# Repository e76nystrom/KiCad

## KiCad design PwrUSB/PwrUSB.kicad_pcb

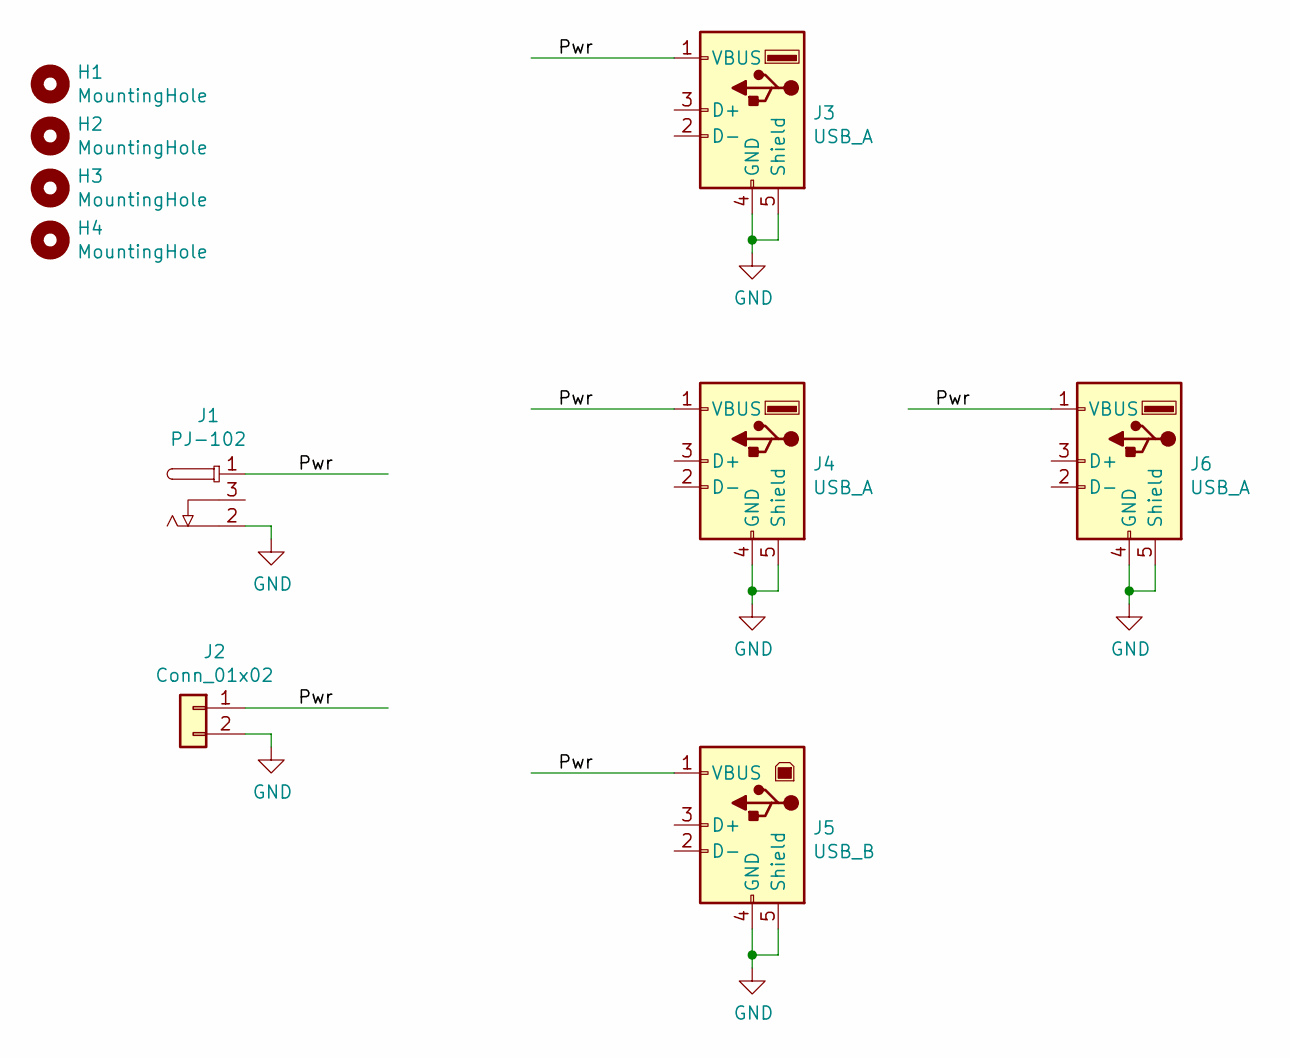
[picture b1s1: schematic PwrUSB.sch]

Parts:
H1, H2, H3, H4: MountingHole; MountingHole _1-8_1-4
J1: PJ-102
J2: Conn_01x02; 2 Pin 3.81mm
J3, J4: USB_A; USB-A
J5: USB_B; USB-B
J6: USB_A; USB-A-Vert

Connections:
/Pwr: J1.1, J2.1, J3.1 (VBUS), J4.1 (VBUS), J5.1 (VBUS), J6.1 (VBUS)
GND: J1.2, J2.2, J3.4 (GND), J3.5 (Shield), J4.4 (GND), J4.5 (Shield), J5.4 (GND), J5.5 (Shield), J6.4 (GND), J6.5 (Shield)

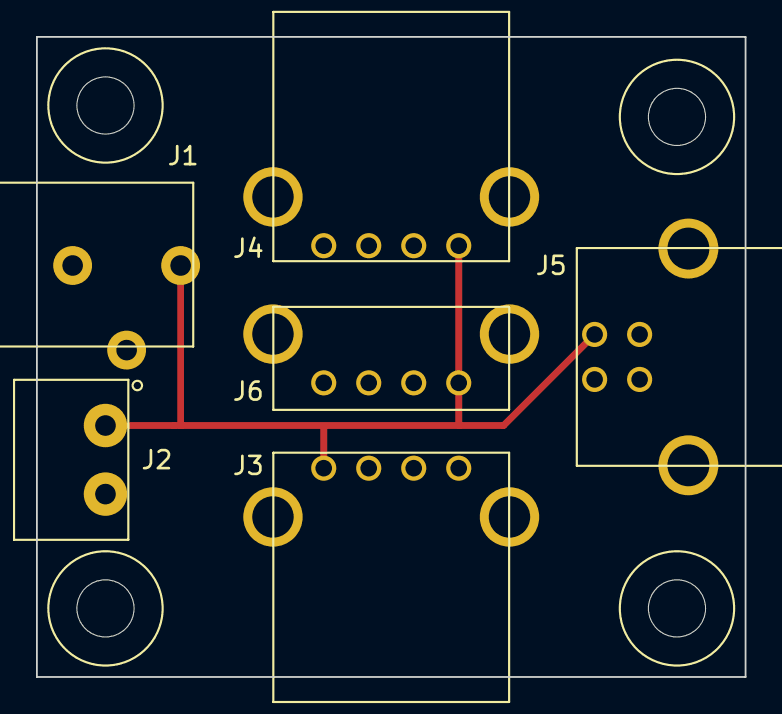
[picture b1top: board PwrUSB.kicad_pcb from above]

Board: 2 copper layers, 39.4 x 35.6 mm, 10 parts (0 on the bottom side), 2 nets.

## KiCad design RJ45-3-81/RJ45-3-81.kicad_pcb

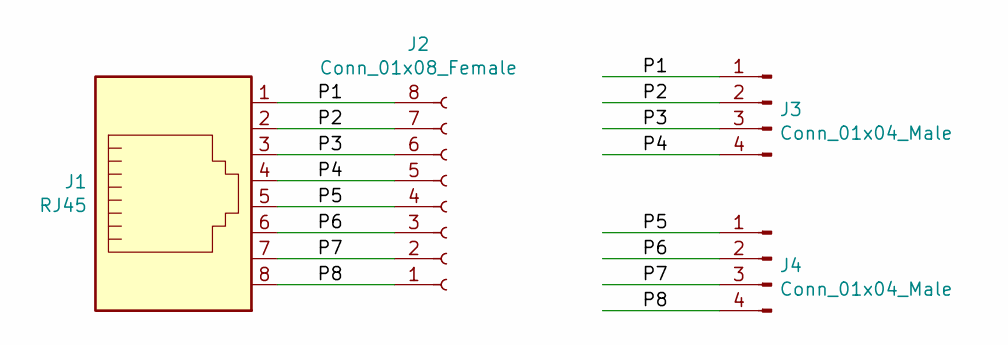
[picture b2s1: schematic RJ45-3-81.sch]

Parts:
J1: RJ45; RJ45_Amphenol_54602-x08_Horizontal
J2: Conn_01x08_Female; PhoenixContact_MC_1,5_8-G-3.81_1x08_P3.81mm_Horizontal
J3, J4: Conn_01x04_Male; PinHeader_1x04_P2.54mm_Vertical

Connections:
/P1: J1.1, J2.8, J3.1
/P2: J1.2, J2.7, J3.2
/P3: J1.3, J2.6, J3.3
/P4: J1.4, J2.5, J3.4
/P5: J1.5, J2.4, J4.1
/P6: J1.6, J2.3, J4.2
/P7: J1.7, J2.2, J4.3
/P8: J1.8, J2.1, J4.4

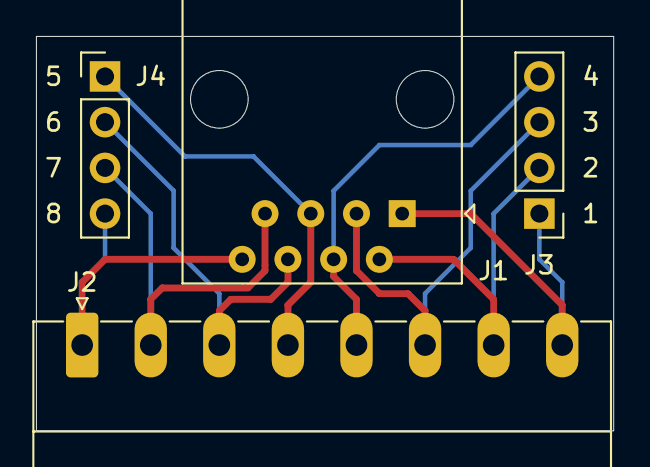
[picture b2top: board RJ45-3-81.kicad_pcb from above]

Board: 2 copper layers, 32.1 x 21.9 mm, 4 parts (0 on the bottom side), 8 nets.

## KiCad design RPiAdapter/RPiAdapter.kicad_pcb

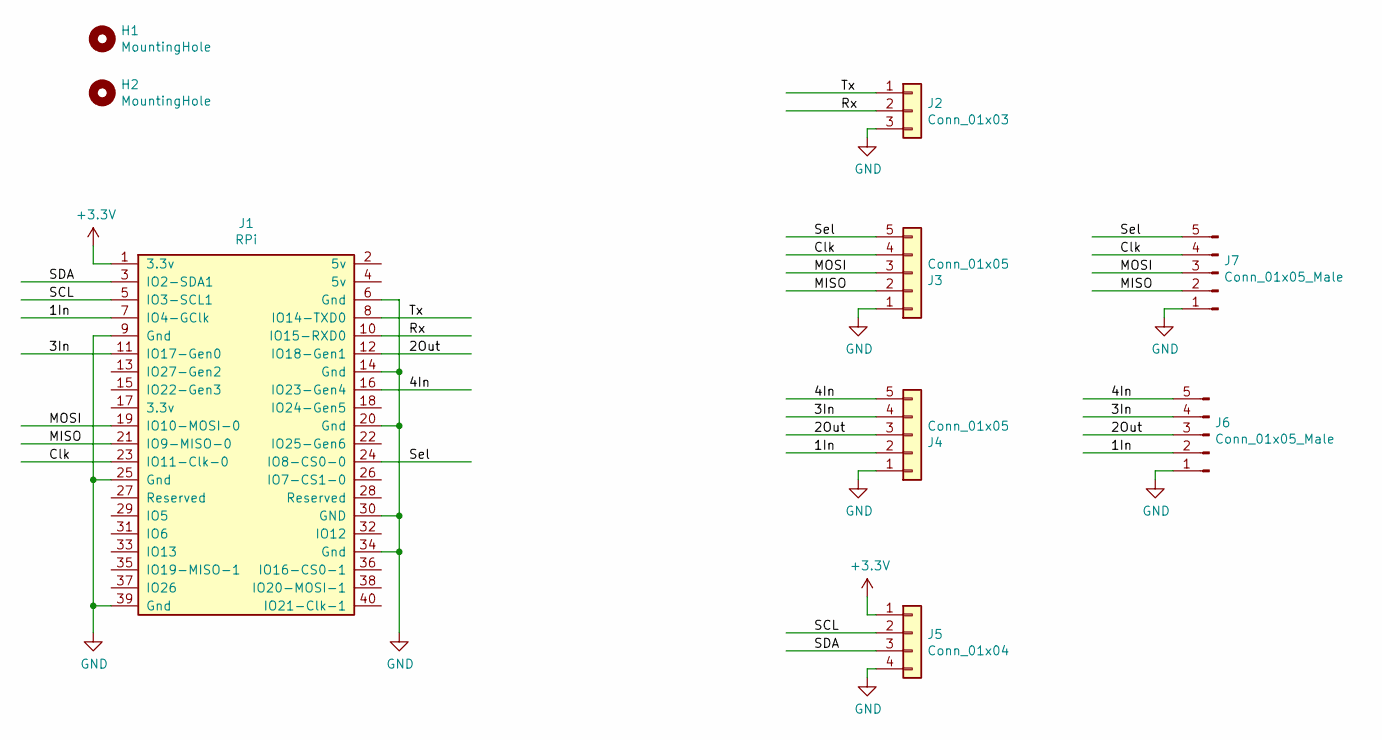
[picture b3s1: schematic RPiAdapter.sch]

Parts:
H1, H2: MountingHole; MountingHole _1-8_1-4
J1: RPi; PinHeader_2x20_P2.54mm_Vertical
J2: Conn_01x03; JST_EH_S3B-EH_1x03_P2.50mm_Horizontal
J3, J4: Conn_01x05; Molex_KK-254_AE-6410-05A_1x05_P2.54mm_Vertical
J5: Conn_01x04; JST_EH_S4B-EH_1x04_P2.50mm_Horizontal
J6, J7: Conn_01x05_Male; PinHeader_1x05_P2.54mm_Vertical

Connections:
+3V3: J1.1 (3.3v), J5.1
/1In: J1.7 (IO4-GClk), J4.2, J6.2
/2Out: J1.12 (IO18-Gen1), J4.3, J6.3
/3In: J1.11 (IO17-Gen0), J4.4, J6.4
/4In: J1.16 (IO23-Gen4), J4.5, J6.5
/Clk: J1.23 (IO11-Clk-0), J3.4, J7.4
/MISO: J1.21 (IO9-MISO-0), J3.2, J7.2
/MOSI: J1.19 (IO10-MOSI-0), J3.3, J7.3
/Rx: J1.10 (IO15-RXD0), J2.2
/SCL: J1.5 (IO3-SCL1), J5.2
/SDA: J1.3 (IO2-SDA1), J5.3
/Sel: J1.24 (IO8-CS0-0), J3.5, J7.5
/Tx: J1.8 (IO14-TXD0), J2.1
GND: J1.6 (Gnd), J1.9 (Gnd), J1.14 (Gnd), J1.20 (Gnd), J1.25 (Gnd), J1.30 (GND), J1.34 (Gnd), J1.39 (Gnd), J2.3, J3.1, J4.1, J5.4, J6.1, J7.1

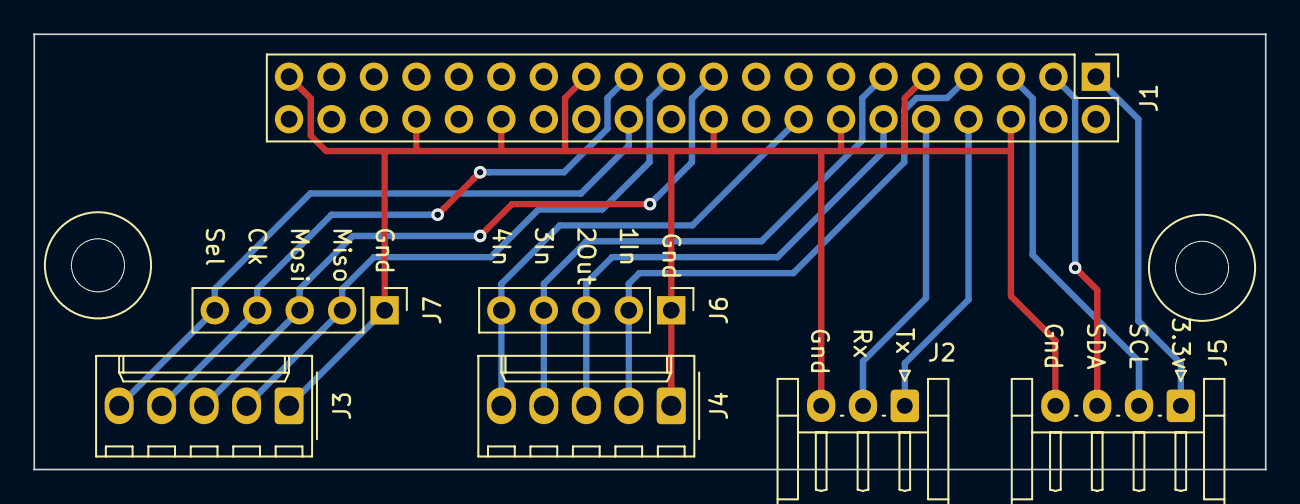
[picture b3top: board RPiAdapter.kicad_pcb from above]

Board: 2 copper layers, 73.7 x 26.0 mm, 9 parts (0 on the bottom side), 14 nets.

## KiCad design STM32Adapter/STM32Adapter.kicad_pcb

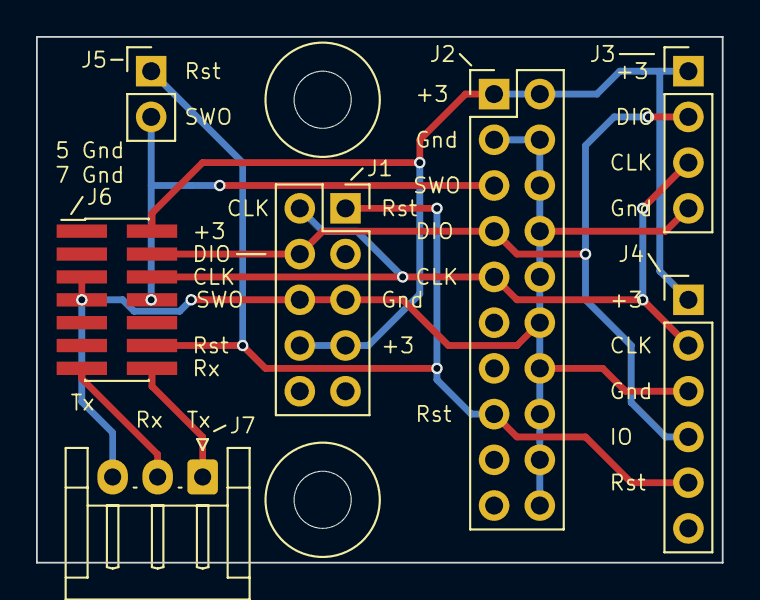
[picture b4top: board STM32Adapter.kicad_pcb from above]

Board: 2 copper layers, 38.1 x 29.2 mm, 9 parts (0 on the bottom side), 8 nets.

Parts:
H1, H2: MountingHole; MountingHole _1-8_1-4
J1: Conn_02x05_Odd_Even; PinSocket_2x05_P2.54mm_Vertical
J2: Conn_02x10_Odd_Even; PinHeader_2x10_P2.54mm_Vertical
J3: Conn_01x04_Male; PinHeader_1x04_P2.54mm_Vertical
J4: Conn_01x06_Male; PinHeader_1x06_P2.54mm_Vertical
J5: Conn_01x02_Male; PinHeader_1x02_P2.54mm_Vertical
J6: Conn_02x07_Odd_Even; PinHeader_2x07_P1.27mm_Vertical_SMD_Samtec
J7: Conn_01x03; JST_EH_S3B-EH_1x03_P2.50mm_Horizontal

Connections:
+3V3: J1.7, J1.8, J2.1, J2.2, J3.1, J4.1, J6.2
/Reset: J1.1, J2.15, J4.5, J5.1, J6.12
/SWCLK: J1.2, J2.9, J3.3, J4.2, J6.6
/SWDIO: J1.4, J2.7, J3.2, J4.4, J6.4
/SWO: J2.5, J5.2, J6.8
/VCP_RX<-TX: J6.14, J7.1
/VCP_TX->RX: J6.13, J7.2
GND: J1.5, J1.6, J2.3, J2.4, J2.6, J2.8, J2.10, J2.12, J2.14, J2.16, J2.18, J2.20, J3.4, J4.3, J6.5, J6.7, J7.3

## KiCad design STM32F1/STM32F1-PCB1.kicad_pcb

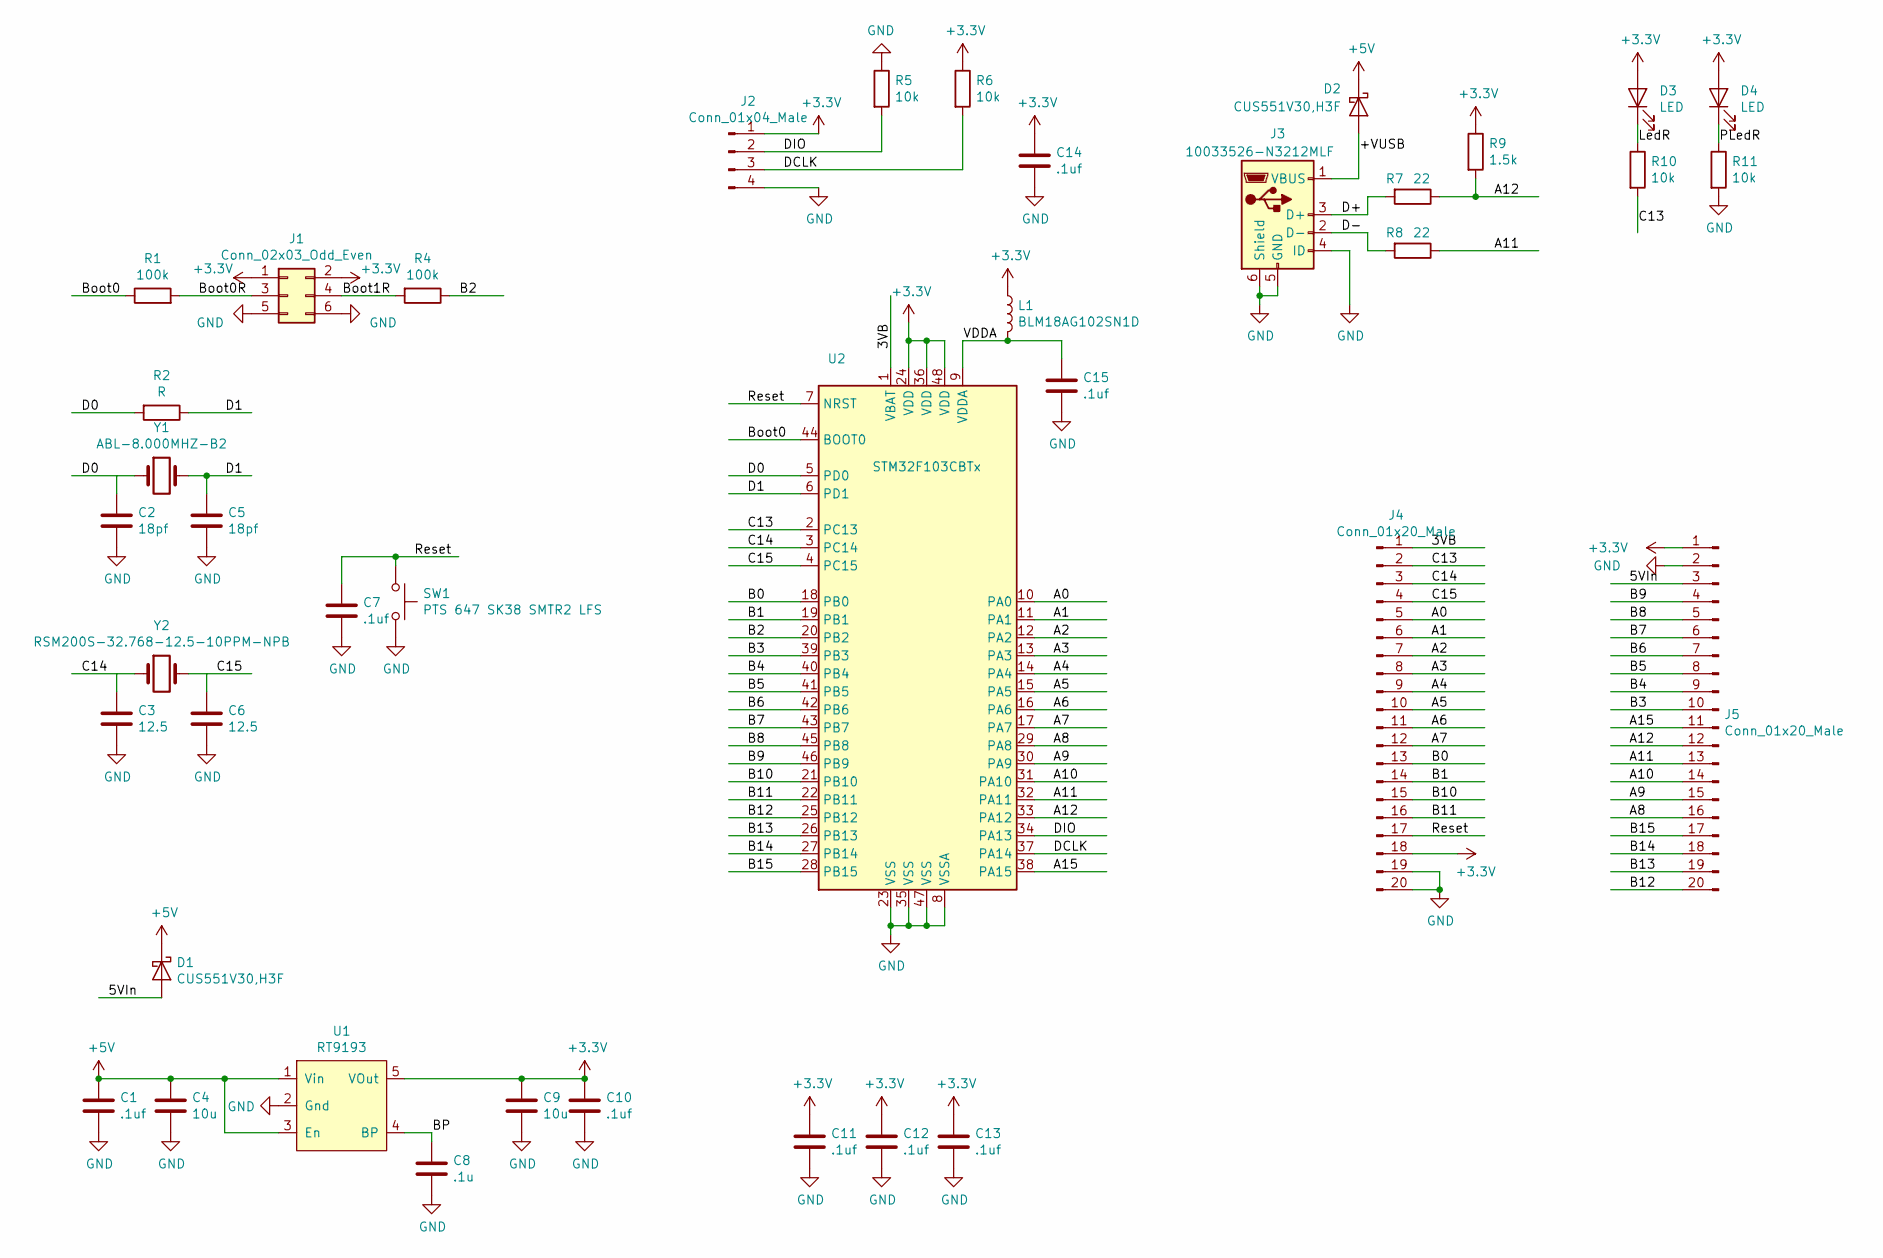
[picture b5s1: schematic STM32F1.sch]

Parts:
C1, C7, C10, C11, C12, C13, C14, C15: .1uf; C_0603_1608Metric_Pad1.05x0.95mm_HandSolder
C2, C5: 18pf; C_0603_1608Metric_Pad1.05x0.95mm_HandSolder
C3, C6: 12.5; C_0603_1608Metric_Pad1.05x0.95mm_HandSolder
C4, C9: 10u; C_0805_2012Metric_Pad1.15x1.40mm_HandSolder
C8: .1u; C_0603_1608Metric_Pad1.05x0.95mm_HandSolder
D1, D2: CUS551V30,H3F; D_SOD-323_HandSoldering
D3, D4: LED; LED_0603_1608Metric_Pad1.05x0.95mm_HandSolder
J1: Conn_02x03_Odd_Even; PinHeader_2x03_P2.54mm_Vertical
J2: Conn_01x04_Male; PinHeader_1x04_P2.54mm_Vertical
J3: 10033526-N3212MLF; USB_Mini_B
J4, J5: Conn_01x20_Male; PinHeader_1x20_P2.54mm_Vertical
L1: BLM18AG102SN1D; L_0603_1608Metric_Pad1.05x0.95mm_HandSolder
R1, R4: 100k; R_0603_1608Metric_Pad1.05x0.95mm_HandSolder
R2: R; R_0603_1608Metric_Pad1.05x0.95mm_HandSolder
R5, R6, R10, R11: 10k; R_0603_1608Metric_Pad1.05x0.95mm_HandSolder
R7, R8: 22; R_0603_1608Metric_Pad1.05x0.95mm_HandSolder
R9: 1.5k; R_0603_1608Metric_Pad1.05x0.95mm_HandSolder
SW1: PTS 647 SK38 SMTR2 LFS; PB_PTS-647
U1: RT9193; SOT-23-5_HandSoldering
U2: STM32F103CBTx; LQFP-48_7x7mm_P0.5mm
Y1: ABL-8.000MHZ-B2‎; Crystal_HC49-4H_Vertical
Y2: RSM200S-32.768-12.5-10PPM-NPB; RSM2000S

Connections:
+3V3: C9.1, C10.1, C11.1, C12.1, C13.1, C14.1, D3.2 (A), D4.2 (A), J1.1, J1.2, J2.1, J4.18, J5.1, L1.1, R6.1, R9.1, U1.5 (VOut), U2.24 (VDD), U2.36 (VDD), U2.48 (VDD)
+5V: C1.1, C4.1, D1.1 (K), D2.1 (K), U1.1 (Vin), U1.3 (En)
/3VB: J4.1, U2.1 (VBAT)
/5VIn: D1.2 (A), J5.3
/+VUSB: D2.2 (A), J3.1 (VBUS)
/A0: J4.5, U2.10 (PA0)
/A1: J4.6, U2.11 (PA1)
/A2: J4.7, U2.12 (PA2)
/A3: J4.8, U2.13 (PA3)
/A4: J4.9, U2.14 (PA4)
/A5: J4.10, U2.15 (PA5)
/A6: J4.11, U2.16 (PA6)
/A7: J4.12, U2.17 (PA7)
/A8: J5.16, U2.29 (PA8)
/A9: J5.15, U2.30 (PA9)
/A10: J5.14, U2.31 (PA10)
/A11: J5.13, R8.1, U2.32 (PA11)
/A12: J5.12, R7.1, R9.2, U2.33 (PA12)
/A15: J5.11, U2.38 (PA15)
/B0: J4.13, U2.18 (PB0)
/B1: J4.14, U2.19 (PB1)
/B2: R4.1, U2.20 (PB2)
/B3: J5.10, U2.39 (PB3)
/B4: J5.9, U2.40 (PB4)
/B5: J5.8, U2.41 (PB5)
/B6: J5.7, U2.42 (PB6)
/B7: J5.6, U2.43 (PB7)
/B8: J5.5, U2.45 (PB8)
/B9: J5.4, U2.46 (PB9)
/B10: J4.15, U2.21 (PB10)
/B11: J4.16, U2.22 (PB11)
/B12: J5.20, U2.25 (PB12)
/B13: J5.19, U2.26 (PB13)
/B14: J5.18, U2.27 (PB14)
/B15: J5.17, U2.28 (PB15)
/BP: C8.1, U1.4 (BP)
/Boot0: R1.1, U2.44 (BOOT0)
/Boot0R: J1.3, R1.2
/Boot1R: J1.4, R4.2
/C13: J4.2, R10.2, U2.2 (PC13)
/C14: C3.1, J4.3, U2.3 (PC14), Y2.1
/C15: C6.1, J4.4, U2.4 (PC15), Y2.4
/D0: C2.1, R2.2, U2.5 (PD0), Y1.1
/D1: C5.1, R2.1, U2.6 (PD1), Y1.2
/D+: J3.3 (D+), R7.2
/D-: J3.2 (D-), R8.2
/DCLK: J2.3, R6.2, U2.37 (PA14)
/DIO: J2.2, R5.2, U2.34 (PA13)
/LedR: D3.1 (K), R10.1
/PLedR: D4.1 (K), R11.1
/Reset: C7.1, J4.17, SW1.1, U2.7 (NRST)
/VDDA: C15.1, L1.2, U2.9 (VDDA)
GND: C1.2, C2.2, C3.2, C4.2, C5.2, C6.2, C7.2, C8.2, C9.2, C10.2, C11.2, C12.2, C13.2, C14.2, C15.2, J1.5, J1.6, J2.4, J3.4 (ID), J3.5 (GND), J3.6 (Shield), J4.19, J4.20, J5.2, R5.1, R11.2, SW1.2, U1.2 (Gnd), U2.8 (VSSA), U2.23 (VSS), U2.35 (VSS), U2.47 (VSS)

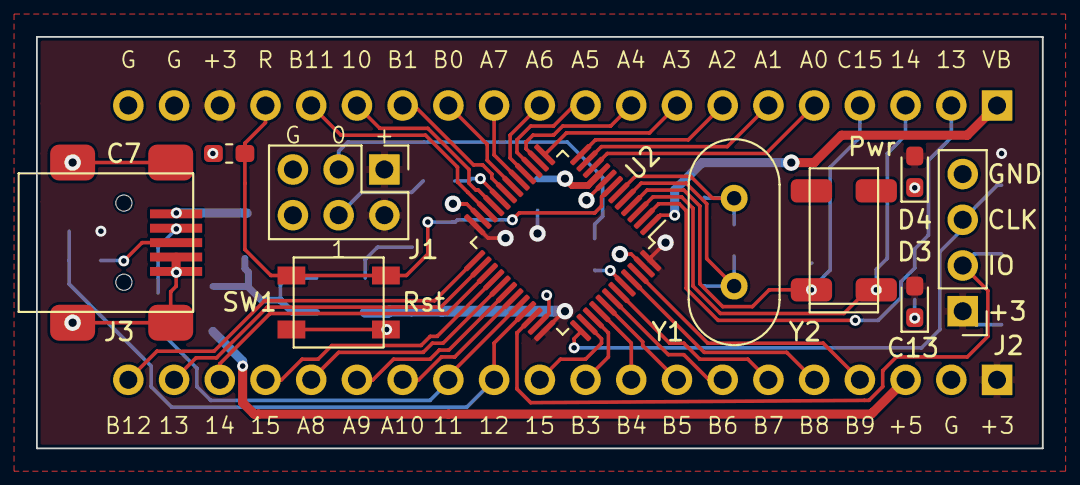
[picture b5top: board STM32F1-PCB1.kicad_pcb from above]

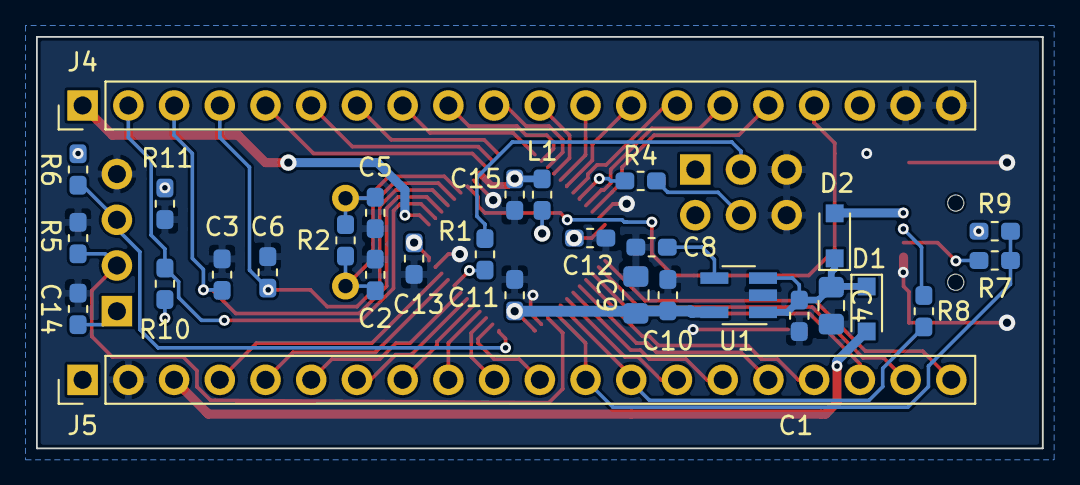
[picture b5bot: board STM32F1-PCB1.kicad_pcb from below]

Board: 2 copper layers, 55.9 x 22.9 mm, 40 parts (30 on the bottom side), 53 nets.
